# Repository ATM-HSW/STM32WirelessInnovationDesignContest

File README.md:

# STM32 Wireless Innovation Design Contest

## Universal room sensor for various MCUs with communication interfaces

### Teaser:

As part of this project, a multi-sensor module is being developed with which various room parameters can be measured. In addition to the usual measured values of temperature, humidity and air pressure, the indoor air quality is also to be determined using VOC and CO2 sensors. A multi-channel light measurement is also to be carried out.

The sensor module should be as compact as possible and be able to be used universally on various MCU platforms via the I2C bus.

Programming should be as simple as possible using existing libraries and software environments, e.g. Arduino environment, Micro- or CircuitPython.

The choice in this competition fell on the relatively new STM32WB52xx platform. Experience with other STM Nucleo boards forms the basis for this project.

### Project Details

The universal room sensor is being developed as the most universal platform possible to measure the parameters of the environment, i.e. rooms such as a lecture theatres, seminar rooms or offices. It should also be possible to test different MCU variants with different communication interfaces and different software environments.

The aim is to equip the rooms of a university with the room sensor. Staff and students should be able to access the sensor values. In future, however, it should also be possible to use the values for needs-based and energy-efficient control of the rooms and integration into the Building Information Management (BIM) system.

### System Overview

As the chosen platform Nucleo-WBA52 is still relatively new, the software support is not yet as extensive as with hardware platforms that have been available for longer. The aim of this project is not the direct use of STM's Cube Packages but of development environments such as Arduino and Circuit-/Micropython. The Python variants are not yet available at the release date 01.03.2024. The Arduino platform STM32duino [sta1] has contained the extension for the STM32WBA family in the main branch since 29/02/2024. However, the planned release 2.8 is not yet available at the time of publication. According to the instructions [sta2], however, a Git branch can also be used for development.

In order to be able to compare the implementation with Circuit- and Micropython, the MultiSensor module was used with the Nucleo-F767 platform, which has been available for some time. This platform can be used in all three environments.

A test shield from a previous project is used to connect the MultiSensor module to the Nucleo-F7676. Only the QWIIC (I2C) connector is used. To connect to the Nucleo-WBA52, a shield has been developed that only provides a QWIIC connector. Due to component availability, the design only includes a short socket strip on which the 3.3V connection is missing. Therefore a 3.3V LDO is used on the board. As this board could not be finalised at the time of publication, a standard QWIIC cable with male jumpers is used to connect the Nucleo board with the MultiSensor module.

Both adapter boards were designed with eagle. The CAD data is available in the project repository at Github (link under software used)

### Sensor hardware

The MultiSensor module contains various sensors for measuring environmental parameters. All sensors are connected to the MCU via an I2C bus. The sensors were selected based on the availability of the ICs and the availability of open source drivers for the development environments analysed. The I2C bus can be used in two ways: on a pin header and via dual QUIIC sockets. As there is an overlap between the I2C addresses of the APDS9960 and AS7341 light sensors, two I2C buses are used. However, both buses are connected by default via solder jumpers. The two solder jumpers only need to be disconnected if both light sensors are to be used. In this case, the APDS9960 is no longer available at the QWIIC sockets, but only via the pin headers.

The only special mechanical feature of the board layout is the thermal decoupling of the two temperature sensors BME680 and HTU21 on the left-hand side of the board.

- Sensor 1: CO2 sensor SCD4x

The SCD-4x CO2 sensors from Sensirion have a measuring range of 400-5000 ppm with different accuracies between ±40 and ±75ppm, depending on the exact type. Versions 40, 41 and 42 are pin and software compatible. As the sensor is based on a photoacoustic measuring principle, it is relatively small and energy-saving compared to older sensors based on the non-dispersive infrared sensor principle [MP]. The ambient air in the measuring chamber is irradiated with a defined light pulse (wavelength approx. 4.3µm). The gas molecules absorb the light. The result is an increase in pressure in the measuring cell. The increase in pressure generates sound waves that can be picked up by a microphone.

For good indoor air quality, the CO2 value should be below 800ppm. The maximum guideline value for indoor spaces is 1500ppm [CIK]. At this value, signs of fatigue can already occur.

- Sensor 2: SGP4x

The SGP-40 and 41 indoor air quality sensors from Sensirion measure volatile organic compounds (VOCs) such as sweat, urea, paint and cleaning agents. The 41 model can also detect nitrogen oxides (NOx). The sensor is a chemical metal oxide semiconductor gas sensor. The surface of the sensor that comes into contact with the gas to be detected is coated with a metal oxide. This changes its resistance, which can be read out as a raw value.

The raw value of the sensor is mapped by a filter function to a measuring range of 0-500, the IAQ index. A value of 100 corresponds to uncontaminated room air.

- Sensor 3: TSL2591 light sensor

The measuring principle of the TSL2591 light sensor from ams is based on two light-to-digital converters that convert the incoming light intensity into electrical signals using photodiodes. The light irradiation changes the electrical voltage measured by the photodiode or the current flowing through the diode. The sensor's two photodiodes measure the part of the light visible to humans and the infrared spectrum in two channels.

- Sensor 4: Temperature, humidity, pressure and gas sensor BME680

The BME680 combination sensor from Bosch is a MEMS sensor that measures the ambient air parameters of temperature, humidity and air pressure. A gas sensor is also included.

- Sensor 5: APDS9960 light sensor

Like sensor 3, the APDS9960 light sensor from Avago can measure light intensity. Colour measurement is also possible. However, in this project the sensor is used for contactless operation, as it can also be used as a proximity sensor and for gesture recognition such as UP-DOWN-RIGHT-LEFT.

- Sensors 6:

The photo shows an assembly variant in which other sensors have not been fitted. The HTU21 is a sensor for temperature and humidity comparable to the BME680. Ambient light measurement can be extended with the two light sensors LTR390 and AS7341. The LTR390 can measure ultraviolet light in two spectra. The AS7341 is sensitive in the visible and near IR range, similar to the TSL2561, but is divided into 11 channels so that colour temperatures can also be determined.

The circuit and layout were designed using eagle. The respective data sheet information and open hardware layouts were generally used from the Adafruit Github account [ada]. The CAD data is available in the project repository at Github (link under Software used)

The CAD data is available on the car's Github account. The hardware is fully tested, including the sensors missing in the figure above.

### Software

- Variant 1: Nucleo-F767 and Micropython

The implementation with Micropython is only a proof of concept due to limitations of the current Micropython implementation. Usable libraries exist for the BME680, HTU21, SGP40 and SCP4x sensors. The Ethernet interface is directly supported by Micropython. A connection to Thingsboard as an IOT cloud is possible.

As expected, the implementation under Micropython is very quick and easy. The firmware can be flashed with the onboard ST-Link. Utilising existing libraries, the sensors are ready for operation in a short time.

However, the division of the flash has proved to be a significant disadvantage. With the default setting. Of the 2Mbyte flash, only around 80kByte are available for Python code. Most of the rest is reserved for the firmware, although this amount is far from being required.

- Variant 2: Nucleo-F767 and Circuitpython

The statements made about variant 1 also apply to variant 2. As essentially only sensors that are also sold by Adafruit are used, the software support is even simpler than under Micropython. However, the same restriction also applies to Circuitpython: the flash size for the Python sources is too small. Another disadvantage is the lack of network support.

#### Summary of variants 1 and 2:

If it were not for the limitation of the flash size, Micro- and Circuitpython could be very good development environments for the use of the MultiSensor. The lack of Ethernet support in Circuitpython is an exclusion criterion if a cloud connection is required.

The MultiSensor, including a cloud connection, could be fully implemented with another MCU platform using the Circuitpyhon environment.

Porting for the NUCLEO-WBA52 platform has not yet taken place, but it can be assumed that this platform can also be used very well under Python. The disadvantage of the flash size is solvable, as there is sufficient unused flash memory available.

- Variant 3: Nucleo-F767 and STM32duino

As the port for the STM32WBAxx family was not yet available at the start of the project, an initial implementation was carried out on the Nucleo-F767. Available Arduino libraries were used for the sensors. With a few minor adjustments to these libraries, all sensors could be used.

- Variant 4: Nucleo-WBA52 and STM32duino

The application developed for variant 3 could be used directly for variant 4. It was only necessary to adapt the I2C pins.

#### Summary of variants 3 and 4:

As the Arduino environment has existed for a very long time, there are many examples, drivers etc. available. Not everything is immediately usable. But changes are usually limited. Due to the unavoidable compile-link-flash cycle, development is significantly less agile than with a Python variant. However, the usage is also possible with an acceptable amount of effort.

The sources of the implementations are available in the project repository at Github (link under Software used).

## Literature:

[ad] Adafruit Industries, LLC. url: www.adafruit.com

[cik] CIK Solutions. Kohlenstoffdioxid in Räumen messen und überwachen. url: https://www.cik-solutions.com/anwendungen/co2-im-innenraum/

[mp] MIROSLAV PISKOR. SCD4x – der kleinste CO2-Sensor. Hrsg. von SOS electronic. 2021-04-15. url: https://www.soselectronic.com/de/articles/sensirion/scd4x-der-kleinste-co2-sensor-2559

[sta1] STM32duino project repository. url: https://github.com/stm32duino

[sta2] STM32duino git repo integratio into Arduino IDE. url: https://github.com/stm32duino/Arduino_Core_STM32/wiki/Using-git-repository

## Used Software

STM32duino

https://github.com/stm32duino/Arduino_Core_STM32/archive/a5135d476018c1d1ea7b33afe86ae29aa416cbf7.zip

Circuitpython

https://downloads.circuitpython.org/bin/nucleo_f767zi/de_DE/adafruit-circuitpython-nucleo_f767zi-de_DE-8.2.10.bin

Micropython

https://micropython.org/resources/firmware/NUCLEO_F767ZI-20240222-v1.22.2.hex

Project sourcen

https://github.com/ATM-HSW/STM32WirelessInnovationDesignContest

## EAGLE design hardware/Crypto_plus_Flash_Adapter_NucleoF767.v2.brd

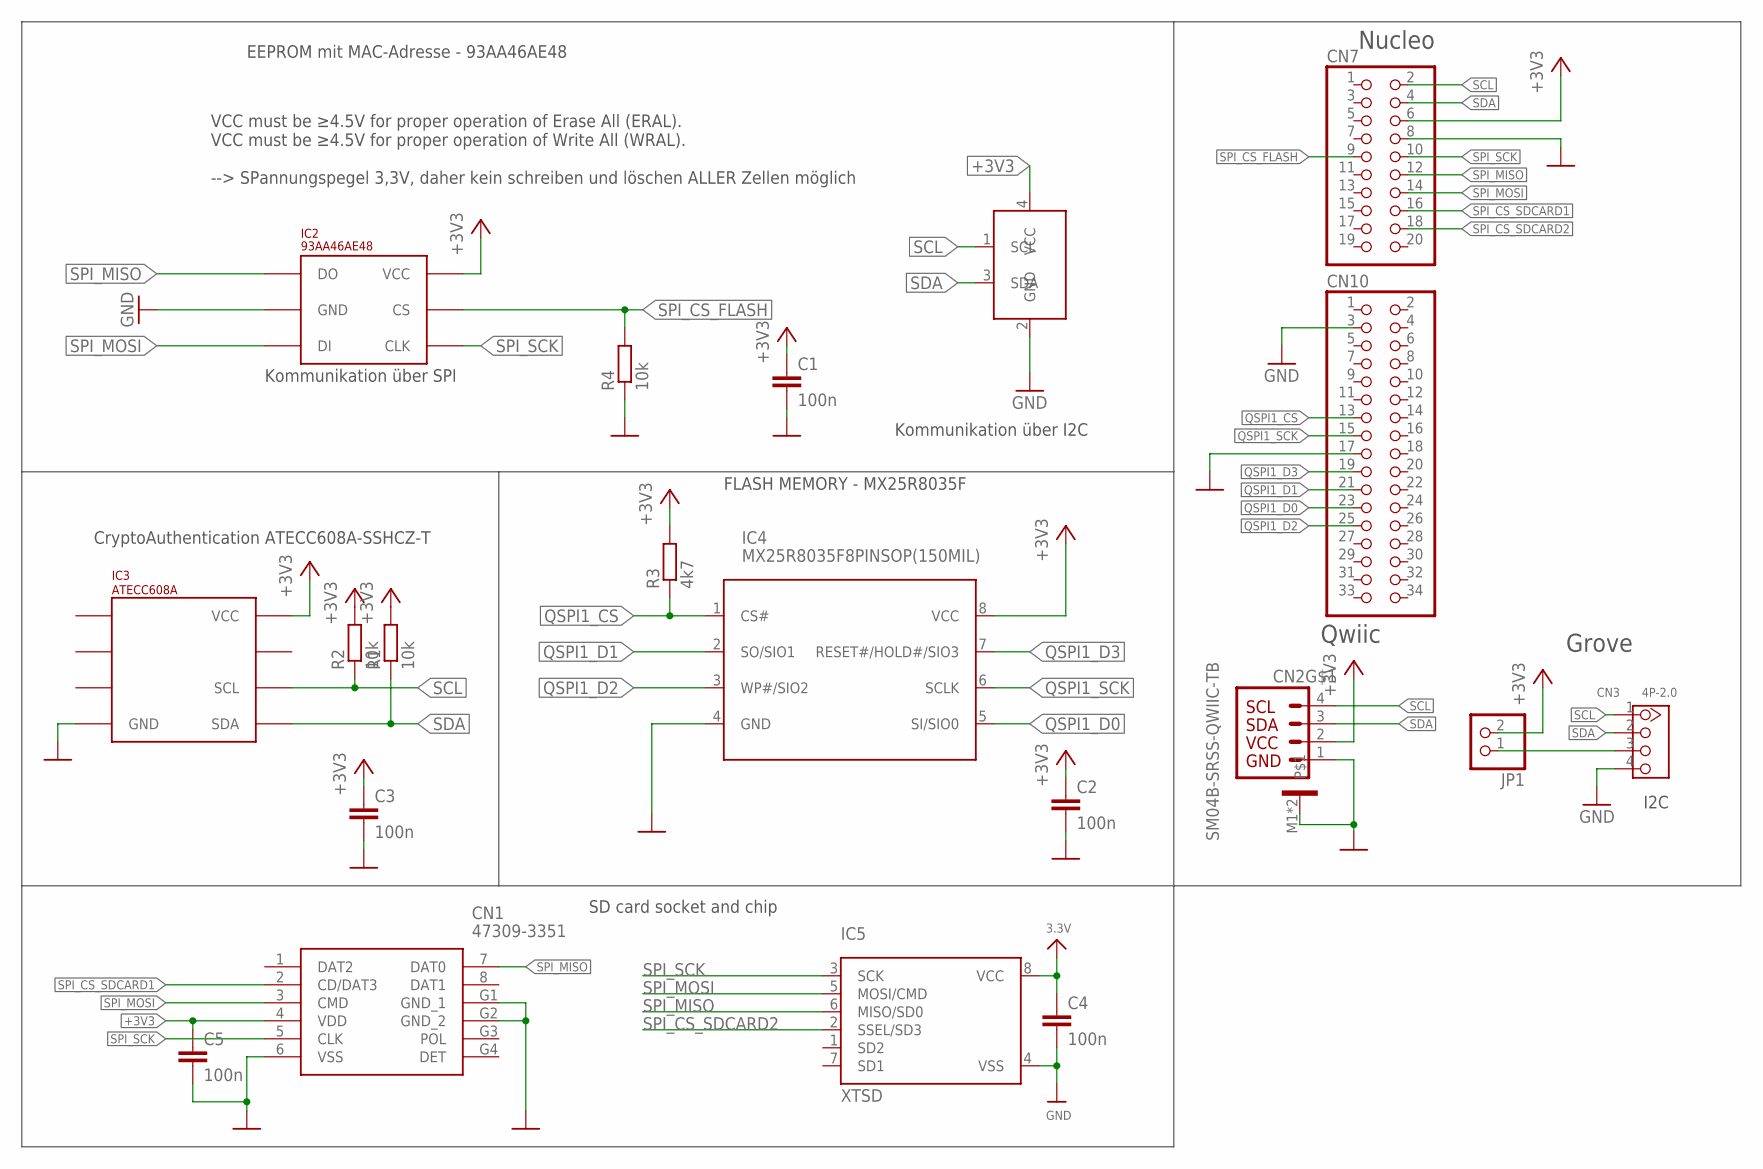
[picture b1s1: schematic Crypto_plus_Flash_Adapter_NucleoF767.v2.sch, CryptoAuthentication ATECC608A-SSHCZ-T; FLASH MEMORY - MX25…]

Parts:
C1, C2, C3, C4, C5: 100n; C0603
CN1: 47309-3351; 473093351
CN2: SM04B-SRSS-QWIIC-TB; SM04B-SRSS-TB
CN3: 4P-2.0; HW4-2.0
CN7: PINHD-2X10; 2X10
CN10: PINHD-2X17; 2X17
IC1: I2CEEPROM_24AA02E48; SOT23-5L
IC2: 93AA46AE48
IC3: ATECC608A; SOIC8
IC4: MX25R8035F8PINSOP(150MIL); SOIC127P600X175-8
IC5: XTSD; LGA8_8X6
JP1: PINHD-1X2; 1X02
R1, R2, R4: 10k; R0603
R3: 4k7; R0603

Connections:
+3V3: C1.1, C2.1, C3.1, C4.1, C5.1, CN1.4 (VDD), CN2.2, CN7.6, IC1.4 (VCC), IC2.P$6 (VCC), IC3.8 (VCC), IC4.8 (VCC), IC5.8 (VCC), JP1.2, R1.2, R2.2, R3.2
GND: C1.2, C2.2, C3.2, C4.2, C5.2, CN1.6 (VSS), CN1.G1 (GND_1), CN1.G2 (GND_2), CN2.1, CN2.M1, CN2.M2, CN3.4, CN7.8, CN10.17, IC1.2 (GND), IC2.P$2 (GND), IC3.4 (GND), IC4.4 (GND), IC5.4 (VSS), R4.1
unnamed: CN3.3, JP1.1
QSPI1_CS: CN10.13, IC4.1 (CS#), R3.1
QSPI1_D0: CN10.23, IC4.5 (SI/SIO0)
QSPI1_D1: CN10.21, IC4.2 (SO/SIO1)
QSPI1_D2: CN10.25, IC4.3 (WP#/SIO2)
QSPI1_D3: CN10.19, IC4.7 (RESET#/HOLD#/SIO3)
QSPI1_SCK: CN10.15, IC4.6 (SCLK)
SCL: CN2.4, CN3.1, CN7.2, IC1.1 (SCL), IC3.6 (SCL), R2.1
SDA: CN2.3, CN3.2, CN7.4, IC1.3 (SDA), IC3.5 (SDA), R1.1
SPI_CS_FLASH: CN7.9, IC2.P$5 (CS), R4.2
SPI_CS_SDCARD1: CN1.2 (CD/DAT3), CN7.16
SPI_CS_SDCARD2: CN7.18, IC5.2 (SSEL/SD3)
SPI_MISO: CN1.7 (DAT0), CN7.12, IC2.P$1 (DO), IC5.6 (MISO/SD0)
SPI_MOSI: CN1.3 (CMD), CN7.14, IC2.P$3 (DI), IC5.5 (MOSI/CMD)
SPI_SCK: CN1.5 (CLK), CN7.10, IC2.P$4 (CLK), IC5.3 (SCK)

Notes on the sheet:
VCC must be ≥4.5V for proper operation of Erase All (ERAL). VCC must be ≥4.5V for proper operation of Write All (WRAL). --> SPannungspegel 3,3V, daher kein schreiben und löschen ALLER Zellen möglich
Kommunikation über SPI
CryptoAuthentication ATECC608A-SSHCZ-T
FLASH MEMORY - MX25R8035F
EEPROM mit MAC-Adresse - 93AA46AE48
Kommunikation über I2C
SD card socket and chip
Qwiic
I2C
Grove
Nucleo

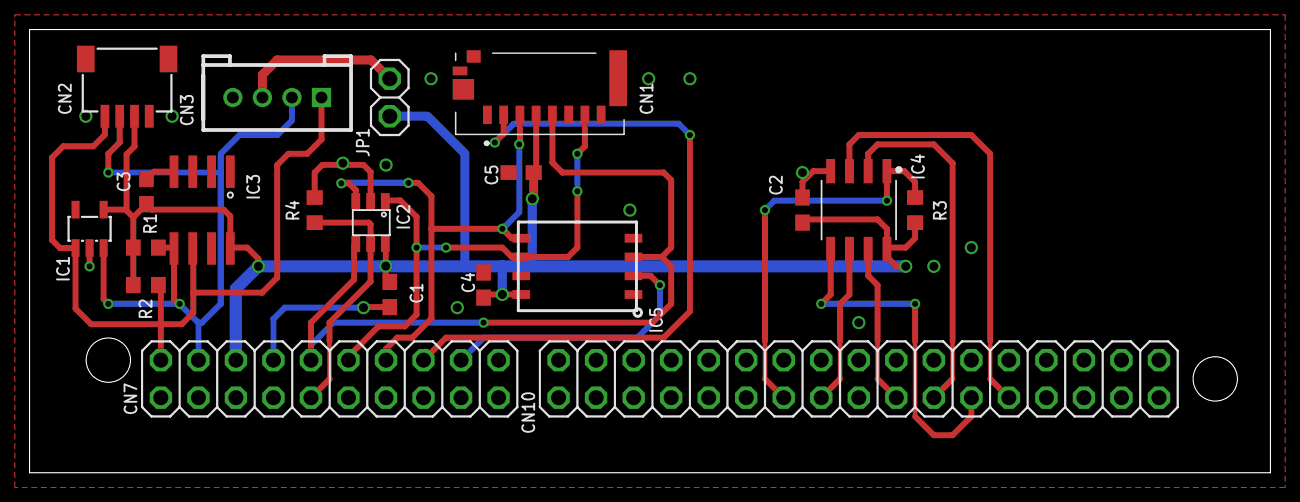
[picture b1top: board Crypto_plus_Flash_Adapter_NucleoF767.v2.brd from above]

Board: 4 copper layers, 84.0 x 30.0 mm, 20 parts (0 on the bottom side), 17 nets.

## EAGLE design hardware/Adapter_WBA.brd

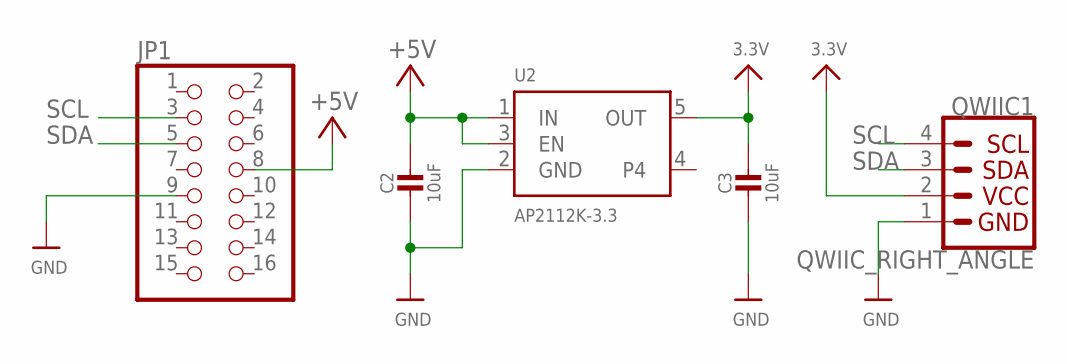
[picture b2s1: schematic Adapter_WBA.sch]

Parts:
C2, C3: 10uF; 0805-NO
JP1: PINHD-2X8; 2X08
QWIIC1: QWIIC_RIGHT_ANGLE; JST04_1MM_RA
U2: AP2112K-3.3; SOT23-5

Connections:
3.3V: C3.1, QWIIC1.2, U2.5 (OUT)
+5V: C2.1, JP1.8, U2.1 (IN), U2.3 (EN)
GND: C2.2, C3.2, JP1.9, QWIIC1.1, U2.2 (GND)
SCL: JP1.3, QWIIC1.4
SDA: JP1.5, QWIIC1.3

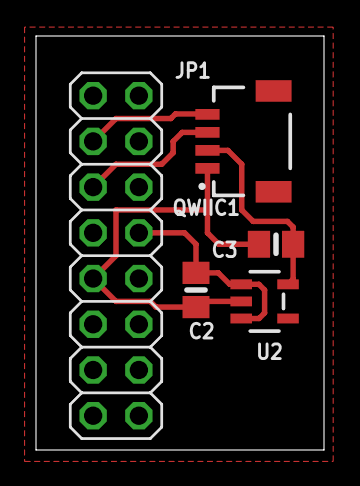
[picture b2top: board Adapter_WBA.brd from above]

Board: 2 copper layers, 16.0 x 23.0 mm, 5 parts (0 on the bottom side), 5 nets.

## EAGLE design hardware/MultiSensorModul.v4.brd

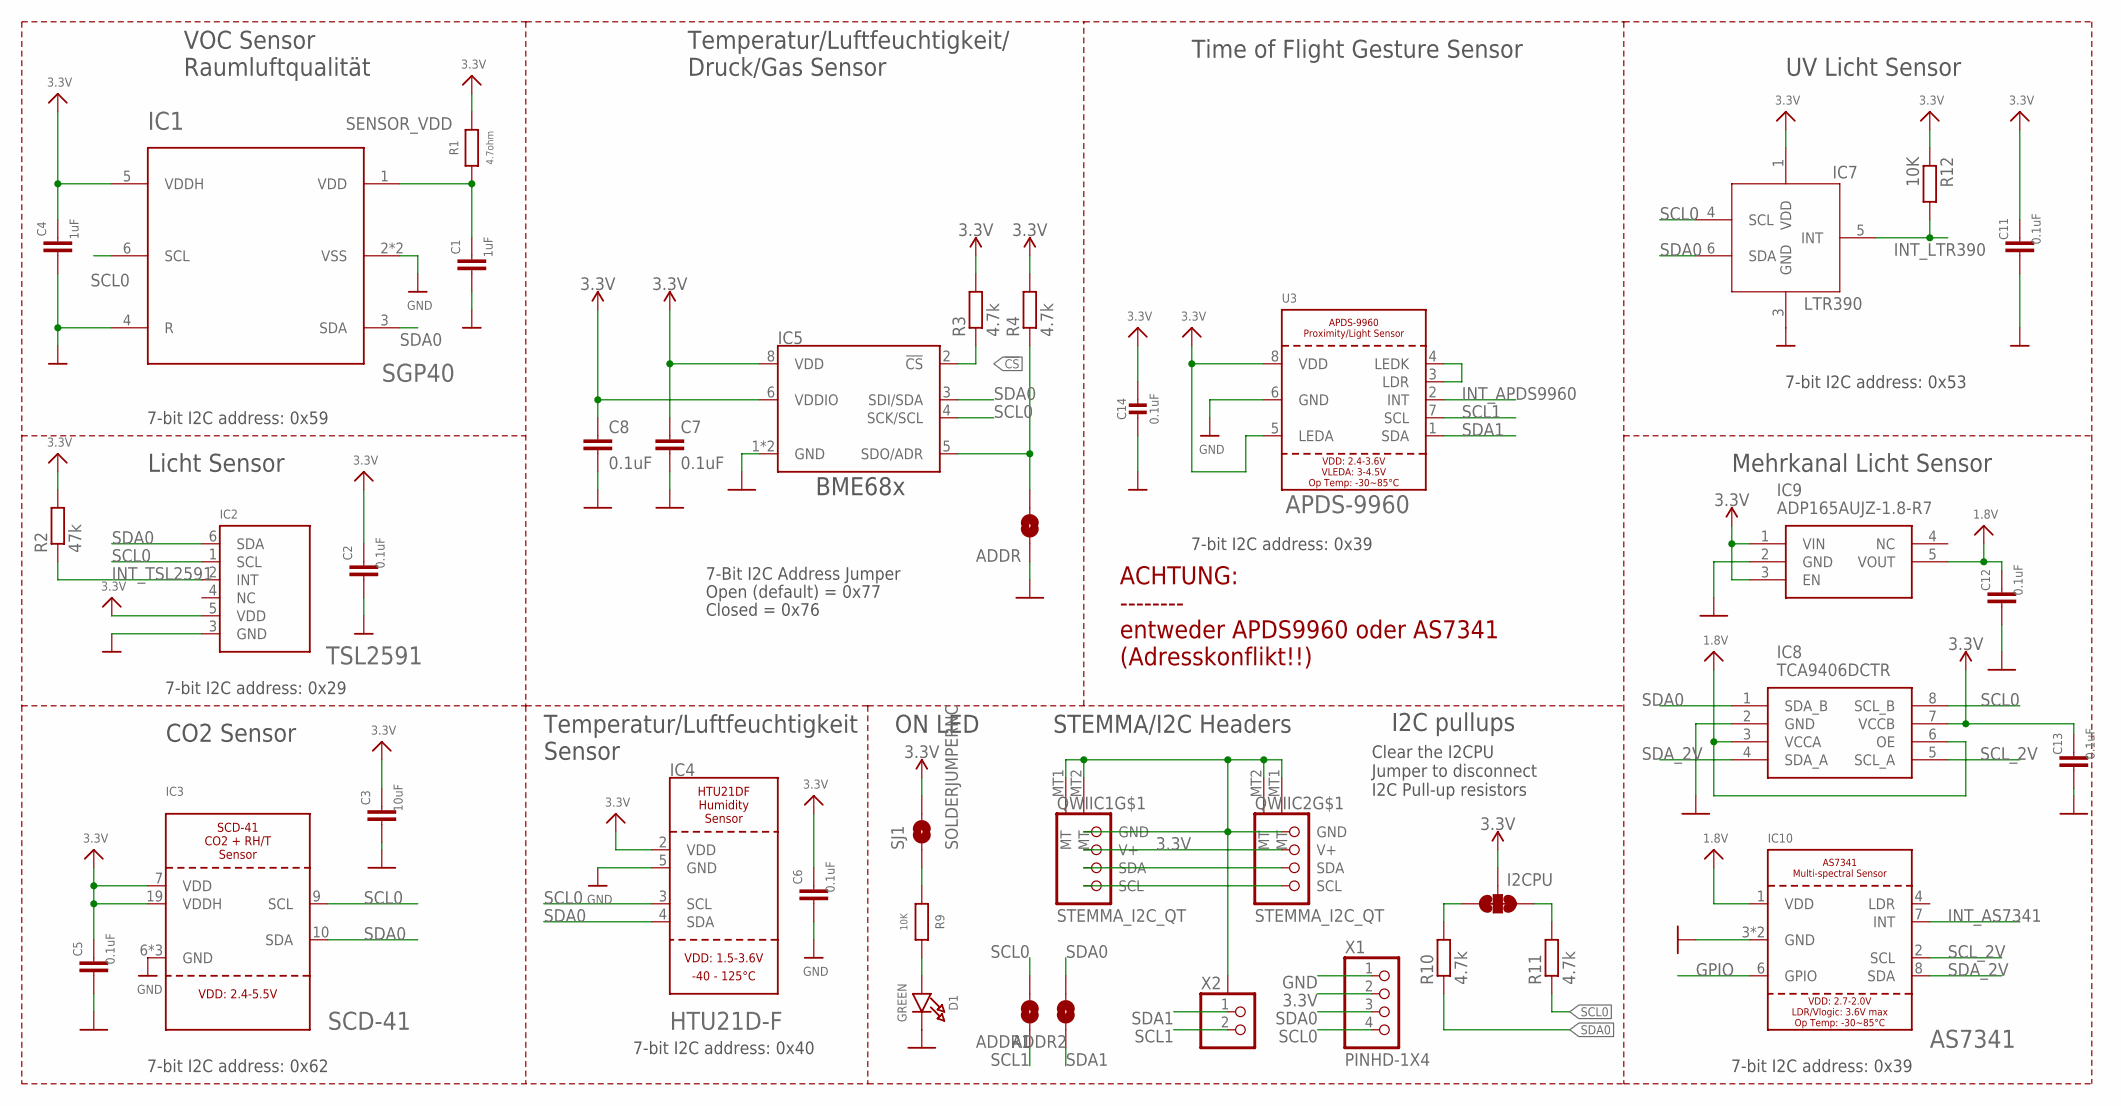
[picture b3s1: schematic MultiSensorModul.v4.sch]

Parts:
ADDR, ADDR1, ADDR2: JUMPER-SMT_2_NO_SILK; SMT-JUMPER_2_NO_SILK
C1, C4: 1uF; C0805
C2, C5, C6, C7, C8, C11, C12, C13: 0.1uF; C0603
C3: 10uF; C0805
C14: 0.1uF; 0603-NO
D1: GREEN; CHIPLED_0603_NOOUTLINE
I2CPU: I2C PU; SMT-JUMPER_3_2-NC_TRACE_SILK
IC1: SGP40; SGP30
IC2: TSL2591; DFN6_TAOS
IC3: SCD-41; SCD41
IC4: HTU21D-F; HTU21DF
IC5: BME680 Air Quality Sensor; LGA3.0X3.0
IC7: LTR390
IC8: TCA9406DCTR; SOP65P400X130-8N
IC9: ADP165AUJZ-1.8-R7; SOT95P280X100-5N
IC10: AS7341
QWIIC1, QWIIC2: STEMMA_I2C_QT; JST_SH4
R1: 4.7ohm; R0603
R2: 47k; R0603
R3, R4, R10, R11: 4.7k; R0603
R9, R12: 10K; R0603
SJ1: SOLDERJUMPERNC; SJ_2S
U3: APDS-9960
X1: PINHD-1X4; 1X04
X2: PINHD-1X2; 1X02

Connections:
1.8V: C12.1, IC8.3 (VCCA), IC8.6 (OE), IC9.5 (VOUT), IC10.1 (VDD)
3.3V: C2.1, C3.1, C4.1, C5.1, C6.1, C7.1, C8.1, C11.1, C13.1, C14.1, I2CPU.2, IC1.5 (VDDH), IC2.5 (VDD), IC3.7 (VDD), IC3.19 (VDDH), IC4.2 (VDD), IC5.6 (VDDIO), IC5.8 (VDD), IC7.1 (VDD), IC8.7 (VCCB), IC9.1 (VIN), IC9.3 (EN), QWIIC1.2 (V+), QWIIC2.2 (V+), R1.2, R2.2, R3.2, R4.2, R12.1, SJ1.2, U3.5 (LEDA), U3.8 (VDD), X1.2
!CS: IC5.2 (!CS), R3.1
GND: ADDR.1, C1.2, C2.2, C3.2, C4.2, C5.2, C6.2, C7.2, C8.2, C11.2, C12.2, C13.2, C14.2, D1.C, IC1.2 (VSS), IC1.4 (R), IC1.P$7 (VSS), IC2.3 (GND), IC3.6 (GND), IC3.20 (GND), IC3.P$1 (GND), IC4.5 (GND), IC5.1 (GND), IC5.7 (GND), IC7.3 (GND), IC8.2 (GND), IC9.2 (GND), IC10.3 (GND), IC10.5 (GND), QWIIC1.1 (GND), QWIIC1.MT1 (MT), QWIIC1.MT2 (MT), QWIIC2.1 (GND), QWIIC2.MT1 (MT), QWIIC2.MT2 (MT), U3.6 (GND), X1.1
GPIO: IC10.6 (GPIO)
INT_APDS9960: U3.2 (INT)
INT_AS7341: IC10.7 (INT)
INT_LTR390: IC7.5 (INT), R12.2
INT_TSL2591: IC2.2 (INT), R2.1
unnamed: D1.A, R9.2
unnamed: U3.3 (LDR), U3.4 (LEDK)
unnamed: R9.1, SJ1.1
unnamed: I2CPU.3, R10.2
unnamed: I2CPU.1, R11.2
SCL0: ADDR1.2, IC1.6 (SCL), IC2.1 (SCL), IC3.9 (SCL), IC4.3 (SCL), IC5.4 (SCK/SCL), IC7.4 (SCL), IC8.8 (SCL_B), QWIIC1.4 (SCL), QWIIC2.4 (SCL), R11.1, X1.4
SCL1: ADDR1.1, U3.7 (SCL), X2.2
SCL_2V: IC8.5 (SCL_A), IC10.2 (SCL)
SDA0: ADDR2.2, IC1.3 (SDA), IC2.6 (SDA), IC3.10 (SDA), IC4.4 (SDA), IC5.3 (SDI/SDA), IC7.6 (SDA), IC8.1 (SDA_B), QWIIC1.3 (SDA), QWIIC2.3 (SDA), R10.1, X1.3
SDA1: ADDR2.1, U3.1 (SDA), X2.1
SDA_2V: IC8.4 (SDA_A), IC10.8 (SDA)
SDO/ADR: ADDR.2, IC5.5 (SDO/ADR), R4.1
SENSOR_VDD: C1.1, IC1.1 (VDD), R1.1

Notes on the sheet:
STEMMA/I2C Headers
ON LED
7-Bit I2C Address Jumper
Open (default) = 0x77
Closed = 0x76
Clear the I2CPU Jumper to disconnect I2C Pull-up resistors
7-bit I2C address: 0x39
Time of Flight Gesture Sensor
I2C pullups
7-bit I2C address: 0x40
7-bit I2C address: 0x62
7-bit I2C address: 0x29
7-bit I2C address: 0x59
7-bit I2C address: 0x53
ACHTUNG: -------- entweder APDS9960 oder AS7341 (Adresskonflikt!!)
VOC Sensor Raumluftqualität
Temperatur/Luftfeuchtigkeit/ Druck/Gas Sensor
UV Licht Sensor
Mehrkanal Licht Sensor
Temperatur/Luftfeuchtigkeit Sensor
CO2 Sensor
Licht Sensor
BME68x

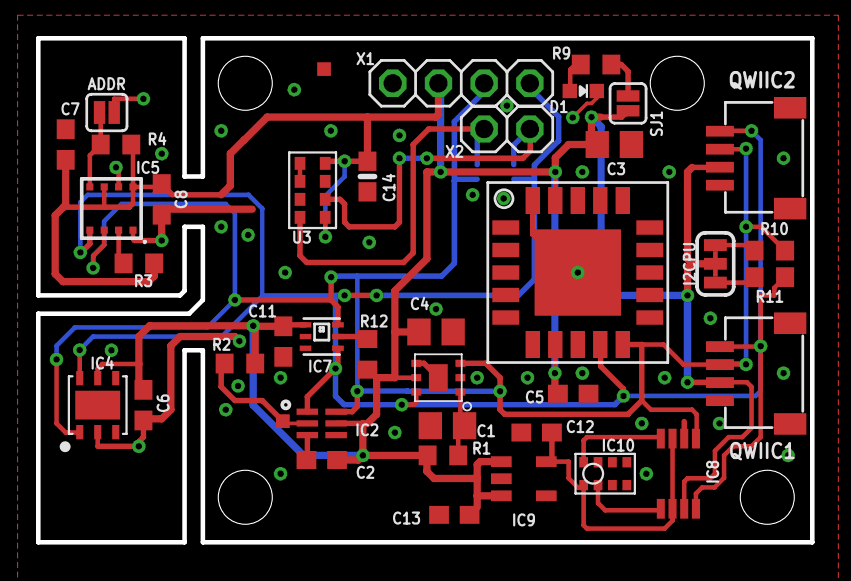
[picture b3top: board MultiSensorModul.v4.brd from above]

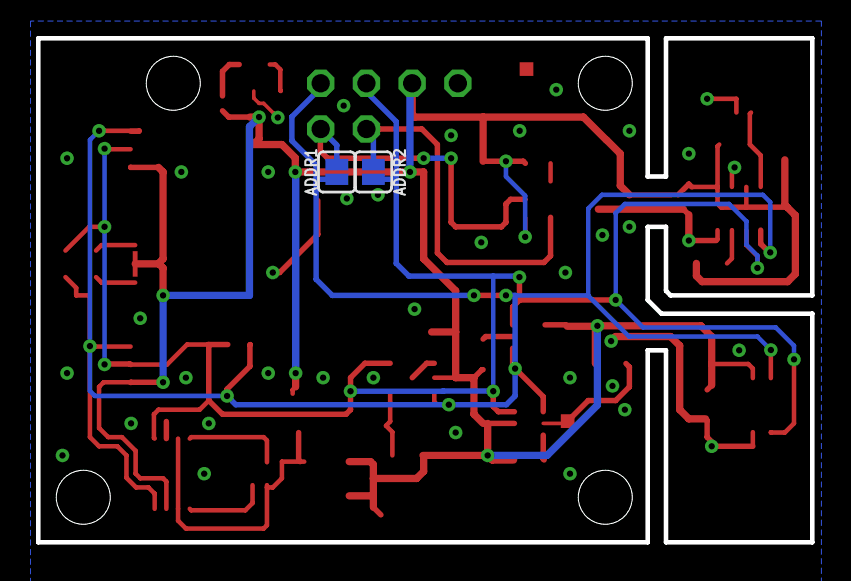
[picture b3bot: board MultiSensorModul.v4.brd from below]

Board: 2 copper layers, 43.0 x 28.0 mm, 40 parts (2 on the bottom side), 19 nets.

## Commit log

2024-03-01 adding firmware, cad data and arduino/python source code
2024-03-01 adding READMEs with used libraries

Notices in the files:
parts and their libraries:
microbuilder: This work is placed in the public domain, and may be freely used for commercial and non-commercial work with the following conditions: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
SparkFun-Connectors: Licensing: Creative Commons ShareAlike 4.0 International - https://creativecommons.org/licenses/by-sa/4.0
